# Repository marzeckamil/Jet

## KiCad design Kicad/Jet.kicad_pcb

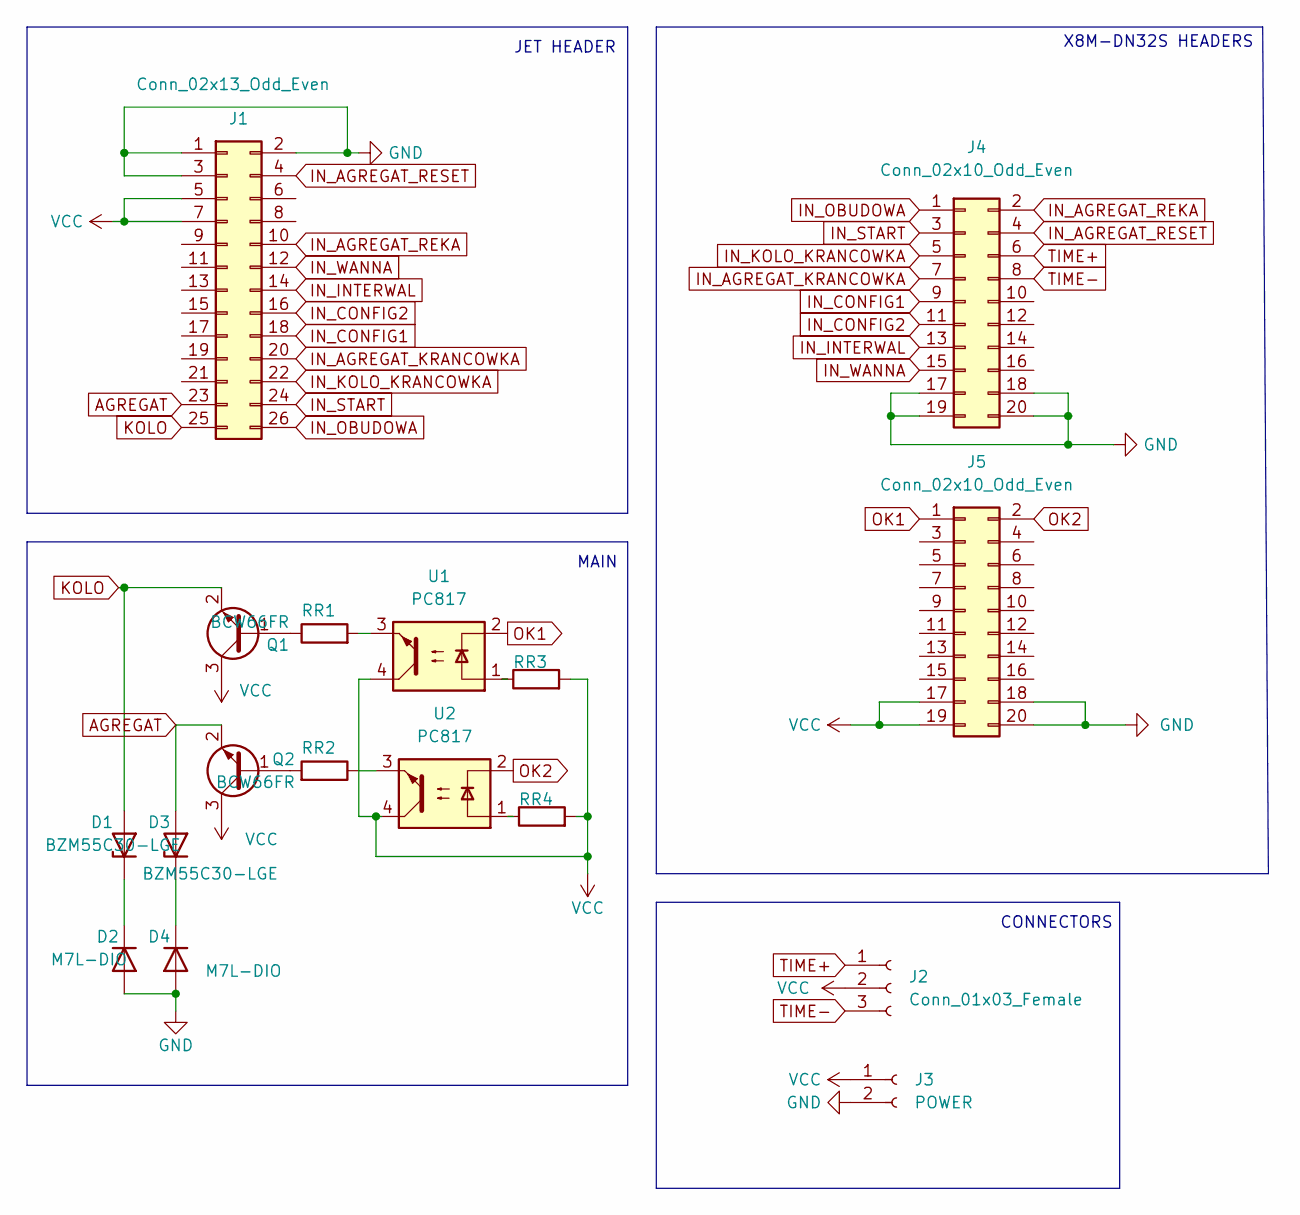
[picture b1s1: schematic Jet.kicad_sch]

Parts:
D1, D3: BZM55C30-LGE; D_MiniMELF
D2, D4: M7L-DIO; D_SMA
J1: Conn_02x13_Odd_Even; IDC-Header_2x13-1MP_P2.54mm_Latch_Horizontal
J2: Conn_01x03_Female; PinSocket_1x03_P2.54mm_Vertical
J3: POWER; PinSocket_1x02_P2.54mm_Vertical
J4, J5: Conn_02x10_Odd_Even; IDC-Header_2x10-1MP_P2.54mm_Latch_Vertical
Q1, Q2: BCW66FR; SOT-23
R1, R2, R3, R4: R; R_0805_2012Metric_Pad1.20x1.40mm_HandSolder
U1, U2: PC817; DIP-4_W7.62mm

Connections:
AGREGAT: D3.2 (A), J1.23, Q2.2 (E)
GND: D2.2 (A), D4.2 (A), J1.1, J1.2, J1.3, J3.2, J4.17, J4.18, J4.19, J4.20, J5.18, J5.20
IN_AGREGAT_KRANCOWKA: J1.20, J4.7
IN_AGREGAT_REKA: J1.10, J4.2
IN_AGREGAT_RESET: J1.4, J4.4
IN_CONFIG1: J1.18, J4.9
IN_CONFIG2: J1.16, J4.11
IN_INTERWAL: J1.14, J4.13
IN_KOLO_KRANCOWKA: J1.22, J4.5
IN_OBUDOWA: J1.26, J4.1
IN_START: J1.24, J4.3
IN_WANNA: J1.12, J4.15
KOLO: D1.2 (A), J1.25, Q1.2 (E)
unnamed: D1.1 (K), D2.1 (K)
unnamed: D3.1 (K), D4.1 (K)
unnamed: Q1.1 (B), R1.1
unnamed: Q2.1 (B), R2.2
unnamed: R1.2, U1.3
unnamed: R2.1, U2.3
unnamed: R3.1, U1.1
unnamed: R4.1, U2.1
OK1: J5.1, U1.2
OK2: J5.2, U2.2
TIME+: J2.1, J4.6
TIME-: J2.3, J4.8
VCC: J1.5, J1.7, J2.2, J3.1, J5.17, J5.19, Q1.3 (C), Q2.3 (C), R3.2, R4.2, U1.4, U2.4

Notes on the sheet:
JET HEADER
CONNECTORS
MAIN
X8M-DN32S HEADERS

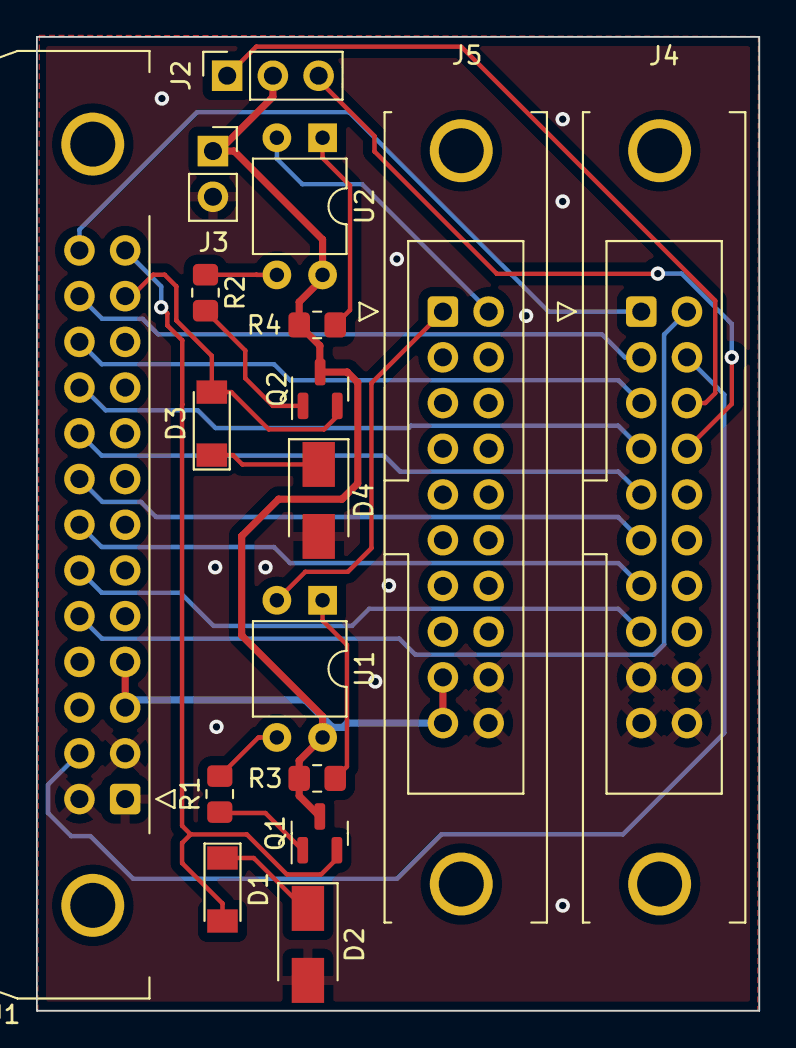
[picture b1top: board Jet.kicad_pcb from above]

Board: 2 copper layers, 40.1 x 54.1 mm, 17 parts (0 on the bottom side), 26 nets.

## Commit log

2023-05-07 First
2023-06-26 UPDATE: footprint
2023-06-28 FIX PCB
2023-07-03 FIX: PCB
2023-07-12 FIX Transistor footprin
2023-07-12 FIX: Paths
